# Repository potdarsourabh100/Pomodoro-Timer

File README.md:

# Pomodoro Timer (STM32 + TM1637 + 18650 Li-ion)

A compact and handheld Pomodoro Timer built using an STM32 microcontroller, TM1637 display, 2 tactile switches, and a buzzer. It is powered by dual 18650 Li-ion cells with a 2S BMS and includes USB charging support.

---

## Pomodoro Timer Flowchart

```text
+----------------------+
|   Start Application |
+----------------------+
           |
           v
+----------------------+
|  Set Work Duration   |<------+
|   (e.g., 25 mins)    |       |
+----------------------+       |
           |                   |
           v                   |
+----------------------+       |
|    Start Work Timer  |       |
+----------------------+       |
           |                   |
           v                   |
+----------------------+       |
|   Countdown Work     |       |
|   Time Every Second  |       |
+----------------------+       |
           |                   |
           v                   |
+----------------------+       |
|  Work Time Finished? |--No--+
+----------------------+
           |
          Yes
           |
           v
+----------------------+
| Play Alarm / Notify |
+----------------------+
           |
           v
+----------------------+
|  Increment Pomodoro  |
|     Count (+1)       |
+----------------------+
           |
           v
+----------------------+
| Pomodoro Count % 4 = 0? |
+----------------------+
       | Yes          | No
       v              v
+----------------+  +----------------------+
| Long Break     |  | Short Break         |
| (15-30 mins)   |  | (5 mins)            |
+----------------+  +----------------------+
       |                   |
       v                   v
+----------------------+  +----------------------+
|  Start Break Timer   |  |  Start Break Timer   |
+----------------------+  +----------------------+
           |                   |
           v                   v
+----------------------+  +----------------------+
| Countdown Break Time |  | Countdown Break Time |
+----------------------+  +----------------------+
           |                   |
           v                   v
+----------------------+  +----------------------+
| Break Time Finished? |  | Break Time Finished? |
+----------------------+  +----------------------+
           |                   |
          Yes                 Yes
           |                   |
           v                   v
+----------------------+
|     Back to Work     |
+----------------------+
           |
           v
     (Repeat Cycle)
```
---

## 🧠 Features

- ⏱️ Pomodoro Mode(P): 25 minutes of focus time
- ☕ Short Break(S): 5 minutes
- 😌 Long Break(L): 15 minutes (after 4 Pomodoros)
- 2 Push Buttons:
  - Button 1: Start/Stop/Reset
  - Button 2: Cycle Modes (P/S/L)
- Buzzer for notifications (end of session, low battery)
- Powered by 2x 18650 Li-ion with BMS protection
- USB Charging (Micro-USB/USB-C)
- TM1637 4-digit 7-segment display

---

## 📦 Hardware Used

| Component       | Description                          |
|----------------|--------------------------------------|
| STM32 MCU      | STM32F0xx / STM32G0xx series         |
| Display        | TM1637 4-digit 7-segment module      |
| Buzzer         | Active piezo buzzer                  |
| Switches       | 2x Tactile push buttons              |
| Battery        | 2x 18650 Li-ion cells                |
| USB Charging   | TP4056-based charger (5V input)      |

---

## 🔧 Build Instructions

1. Assemble all hardware components as per the schematic.
2. Flash the firmware to the STM32 using ST-Link.
3. Power the system using a battery or USB.
4. Use Button 1 to start/stop/reset the timer.
5. Use Button 2 to switch between Pomodoro, Short, and Long Break modes.

---

## 📌 To-Do / Enhancements

- [ ] Add various tones for notifications
- [ ] Add BLE support for app notifications
- [ ] Configurable timer durations via USB
- [ ] Battery monitoring via ADC
- [ ] Low-power sleep mode
- [ ] Pocket-sized, portable enclosure

---

## 📜 License

This project is open-source under the MIT License.

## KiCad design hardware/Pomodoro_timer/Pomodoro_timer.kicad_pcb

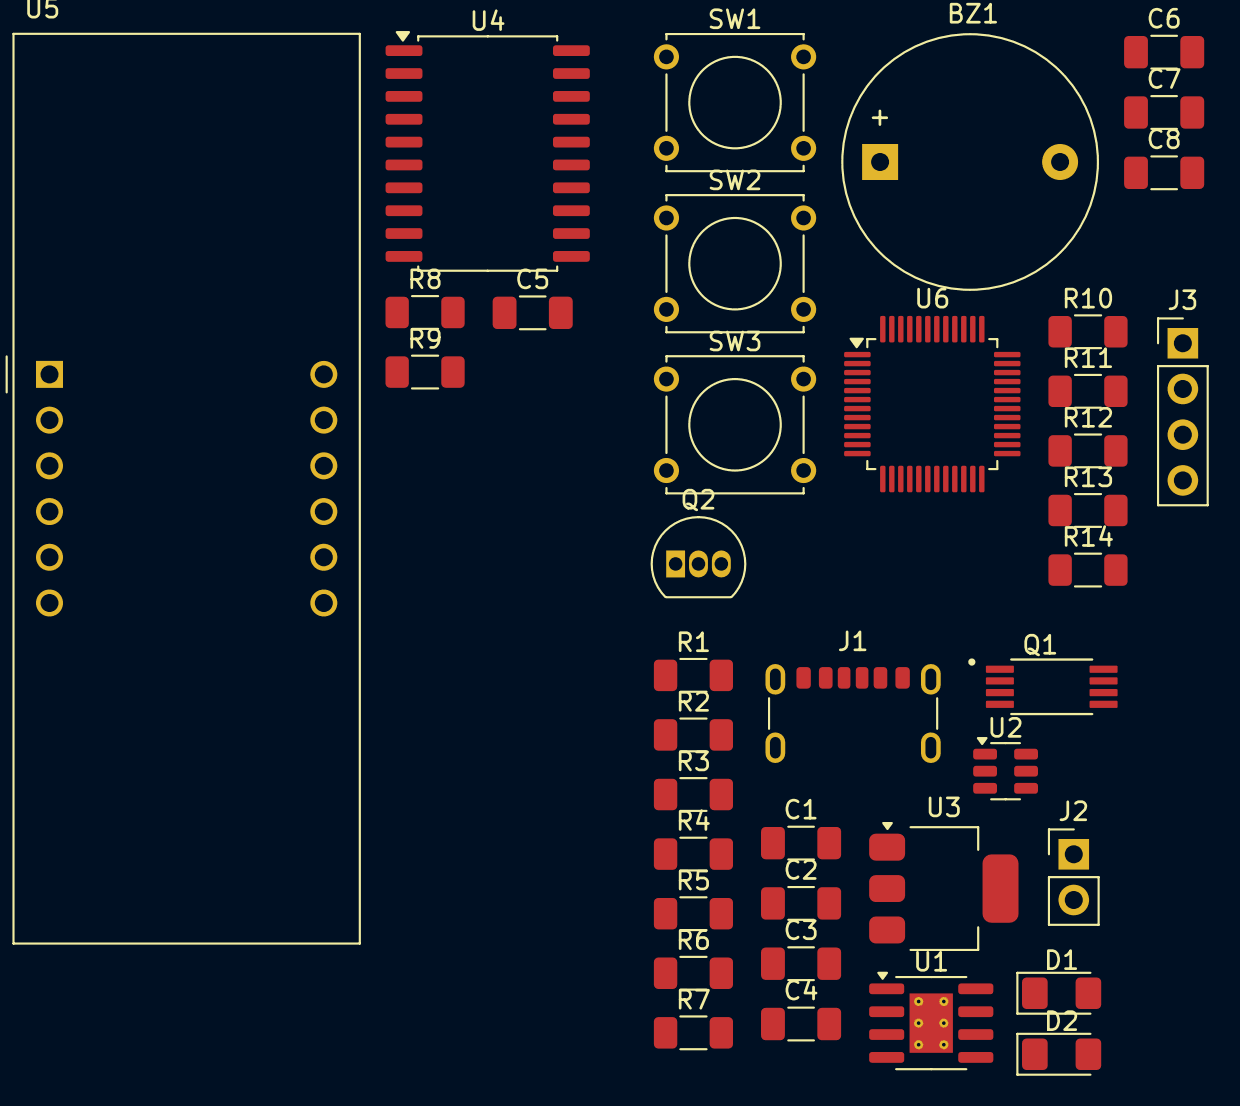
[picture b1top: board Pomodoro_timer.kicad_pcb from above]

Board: 2 copper layers, 39 parts (0 on the bottom side), 38 nets, no tracks yet.

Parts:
BZ1: Buzzer; Buzzer_D14mm_H7mm_P10mm
C1, C3, C4, C5, C6, C7, C8: 100nF; C_1206_3216Metric_Pad1.33x1.80mm_HandSolder
C2: 10uF; C_1206_3216Metric_Pad1.33x1.80mm_HandSolder
D1: RED; LED_1206_3216Metric_Pad1.42x1.75mm_HandSolder
D2: GRN; LED_1206_3216Metric_Pad1.42x1.75mm_HandSolder
J1: USB_C_Receptacle_PowerOnly_6P; USB_C_Receptacle_GCT_USB4125-xx-x_6P_TopMnt_Horizontal
J2: Battery; PinHeader_1x02_P2.54mm_Vertical
J3: Prog_Port; PinHeader_1x04_P2.54mm_Vertical
Q1: FS8205A; SOP65P640X120-8N
Q2: BC516; TO-92_Inline
R1, R2: 5K1; R_1206_3216Metric_Pad1.30x1.75mm_HandSolder
R3, R4, R6, R10: 1K; R_1206_3216Metric_Pad1.30x1.75mm_HandSolder
R5: 1K2; R_1206_3216Metric_Pad1.30x1.75mm_HandSolder
R7: 100; R_1206_3216Metric_Pad1.30x1.75mm_HandSolder
R8, R9, R11, R12, R13, R14: 4K7; R_1206_3216Metric_Pad1.30x1.75mm_HandSolder
SW1, SW2: CTRL_SW; SW_Tactile_Straight_KSA0Axx1LFTR
SW3: FUNC_SW; SW_Tactile_Straight_KSA0Axx1LFTR
U1: TP4056-42-ESOP8; SOIC-8-1EP_3.9x4.9mm_P1.27mm_EP2.41x3.3mm_ThermalVias
U2: DW01A; SOT-23-6
U3: AP2127K-3.3; SOT-223-3_TabPin2
U4: TM1637; SOIC-20W_7.5x12.8mm_P1.27mm
U5: CC56-12EWA; CA56-12EWA
U6: STM32G070CBTx; LQFP-48_7x7mm_P0.5mm

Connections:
+5V: C1.1, D1.2 (A), D2.2 (A), J1.A9 (VBUS), J1.B9 (VBUS), U1.4 (V_{CC}), U1.8 (CE)
CLK: R9.2, U4.18 (CLK), U6.26 (PB14)
DIO: R8.2, U4.17 (DIO), U6.27 (PB15)
GND: C1.2, C2.2, C3.2, C4.2, C5.2, C6.2, C7.2, C8.2, J1.A12 (GND), J1.B12 (GND), J1.S1 (SHIELD), J3.4, Q1.6, Q1.7, Q2.3 (E), R1.1, R2.1, R5.1, R6.1, SW1.1, SW2.2, SW3.2, U1.1 (TEMP), U1.3 (GND), U2.6 (GND), U3.2 (GND), U4.1 (GND), U6.7 (VSS)
unnamed: BZ1.2 (-), Q2.1 (C)
unnamed: D1.1 (K), R3.1
unnamed: D2.1 (K), R4.1
unnamed: J1.A5 (CC1), R2.2
unnamed: J1.B5 (CC2), R1.2
unnamed: C3.1, J2.1, R7.1, U1.5 (BAT), U3.1 (VIN), U3.3 (EN)
unnamed: J2.2, Q1.2, Q1.3
unnamed: Q2.2 (B), R10.2
unnamed: R5.2, U1.2 (PROG)
unnamed: R3.2, U1.7 (~CHRG)
unnamed: R4.2, U1.6 (~STDBY)
unnamed: R6.2, U2.2 (CS)
unnamed: Q1.5, U2.3 (OC)
unnamed: Q1.4, U2.1 (OD)
unnamed: C2.1, R7.2, U2.5 (VCC)
unnamed: U4.15 (GRID1), U5.12 (CC1)
unnamed: U4.14 (GRID2), U5.9 (CC2)
unnamed: U4.13 (GRID3), U5.8 (CC3)
unnamed: U4.12 (GRID4), U5.6 (CC4)
unnamed: U4.2 (SEG1/KS1), U5.11 (a)
unnamed: U4.3 (SEG2/KS2), U5.7 (b)
unnamed: U4.4 (SEG3/KS3), U5.4 (c)
unnamed: U4.5 (SEG4/KS4), U5.2 (d)
unnamed: U4.6 (SEG5/KS5), U5.1 (e)
unnamed: U4.7 (SEG6/KS6), U5.10 (f)
unnamed: U4.8 (SEG7/KS7), U5.5 (g)
unnamed: U4.9 (SEG8/KS8), U5.3 (DPX)
unnamed: R12.1, SW1.2, U6.10 (NRST)
unnamed: R14.1, SW2.1, U6.24 (PB12)
unnamed: R13.1, SW3.1, U6.25 (PB13)
unnamed: R10.1, R11.1, U6.3 (PC15)
PWR: BZ1.1 (+), C4.1, C5.1, C6.1, C7.1, C8.1, J3.3, R8.1, R9.1, R11.2, R12.2, R13.2, R14.2, U4.16 (VDD), U6.4 (VBAT), U6.5 (VREF+), U6.6 (VDD)
SWCLK: J3.1, U6.36 (PA14)
SWDIO: J3.2, U6.35 (PA13)

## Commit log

2025-04-15 Initial release
2025-04-15 Rearranged text correctly & added linting to make file more readable
2025-04-18 Added changelog & firmware with common files
2025-04-20 Given firmware added with TM1637 drivers & tested with 1 second timer.
2025-04-21 Basic timer functionalities & button operations are verified
2025-04-22 POC verified moving to Hardware design
2025-05-10 making necessary changes
2025-05-15 Making changes in documentation
2025-05-15 Adding license for open source
2025-05-31 File rearrangement needed so added. Also files written in new files.
2025-06-22 All pieces for prototype are designed & soldered on PCB.
    The given hardware is working with code.
2025-06-22 ## [1.0.0] - 2025-06-22
    ### 🚀 Initial Release
    - Core Pomodoro functionality (25/5/15 minute cycles)
    ---
    ### ⚠️ Warning/Notice
    - Button-related activities are started.
    - The pause function is yet to be added.
2025-06-22 Added comments for better understanding
2025-06-22 ## [1.0.1] - 2025-06-22
    ### 🐞 Bug fix
    - The timer was not performing correct mode in the proper order
    fixed
    ### ⚠️ Warning/Notice
    - Button-related activities are started.
    - The pause function is yet to be added.
2025-06-22 Board designing started
2025-06-22 TM1637 Design started
2025-07-14 ## [1.2.0] - 2025-07-14
    ### 🐞 Bug fix
    - The given platform dependencies are removed
    - Buzzer functionalities added
    ### ⚠️ Warning/Notice
    - The pause function is yet to be added.
    ### 💤 Power/Performance
2025-07-16 ## [1.2.2] - 2025-07-16
    ### 🐞 Bug fix
    - The values for cycles changed to 5 correct Logic implemented.
    ### ⚠️ Warning/Notice
    - The pause function is yet to be added.
    ### 💤 Power/Performance
    - Although the initial performance looks good
2025-08-04 PCB Ver.A : The Schematic completed the next part for PCB can be started.
2025-08-06 PCB Ver.A The required changes were not in line So made few alterations Need to start again
2025-08-13 PCB Ver.A All changes finalized & PCB design has been started
